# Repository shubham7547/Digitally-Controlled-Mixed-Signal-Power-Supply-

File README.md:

# Digitally Controlled Mixed-Signal Power Supply

[-orange.svg)]()

A high-performance, digitally controlled benchtop power supply that bridges digital precision with an ultra-fast analog regulation loop. The system delivers an adjustable **0 to 30.0 V** output at up to **1.0 A**, featuring dual rotary quadrature encoders with digit-level selection, high-resolution readbacks on a 2.8" color TFT display, and a non-blocking embedded firmware architecture.

Developed at the **Centre for Electronic Design and Technology (CEDT)**, **Netaji Subhas University of Technology (NSUT), New Delhi**.

---

## Table of Contents

- [Architectural Philosophy](#architectural-philosophy)
- [System Architecture](#system-architecture)
- [Key Specifications](#key-specifications)
- [Hardware & Circuit Design](#hardware--circuit-design)
  - [1. AC Input & Bulk Rectification](#1-ac-input--bulk-rectification)
  - [2. Dual Auxiliary Buck Regulators](#2-dual-auxiliary-buck-regulators)
  - [3. Digital Setpoint Generation](#3-digital-setpoint-generation)
  - [4. Analog Voltage Regulation Loop](#4-analog-voltage-regulation-loop)
  - [5. Current Sensing & Differential Amplification](#5-current-sensing--differential-amplification)
- [Pin Assignment Table](#pin-assignment-table)
- [Firmware Architecture](#firmware-architecture)
  - [Interrupt-Driven Quadrature Decoding](#interrupt-driven-quadrature-decoding)
  - [Non-Blocking Scheduling](#non-blocking-scheduling)
  - [Software Current Limit Foldback](#software-current-limit-foldback)
- [Repository Structure](#repository-structure)
- [Getting Started](#getting-started)
  - [Required Libraries](#required-libraries)
  - [Hardware Setup & Flashing](#hardware-setup--flashing)
- [Author & Affiliation](#author--affiliation)
- [License](#license)

---

## Architectural Philosophy

Simpler DIY microcontroller-based power supplies often place the digital microcontroller inside the primary feedback loop or use PWM/software loops to regulate output voltage, leading to slow transient response, ADC latency, and stability issues.

This design enforces a strict separation of concerns:
1. **Digital Setpoint Domain:** The **Arduino Nano** and **TLC5618A 12-bit DAC** determine what target voltage/current limit is desired. They never carry load current and never sit directly inside the fast closed loop.
2. **Analog Control Domain:** An **LM358 op-amp error amplifier** continuously compares the scaled output feedback against the DAC setpoint in real time, driving high-power series-pass transistors (**MJE2955T PNP**) instantaneously without digital latency.

---

## System Architecture

```mermaid
flowchart TD
    Mains["Mains 230V AC"] --> T1["Step-Down Transformer\n(Off-Board)"]
    T1 --> Bridge["Bridge Rectifier (1N4007)\n+ 2x 4700µF Series Caps (50V eff.)"]
    Bridge --> RawDC["Raw DC Bus (~36V Peak)"]

    RawDC --> VR6["LM2575 Buck 1\nStep-down to 5.29V"]
    VR6 --> MCU["Arduino Nano\n(5V Digital Rail)"]

    RawDC --> VR5["LM2575 Buck 2\nStep-down to 30.0V Rail"]
    VR5 --> OpAmp["LM358 Error Amplifier\n(Analog Rail)"]

    MCU -->|Hardware SPI| DAC["TLC5618A 12-Bit DAC\n(Vref Generation)"]
    DAC -->|Vref Setpoint| OpAmp

    RawDC --> PassTrans["MJE2955T Power Transistor\nSeries-Pass Output Stage"]
    OpAmp -->|Drive Base| PassTrans

    PassTrans --> Load["Output Terminal (0–30V, 0–1A)"]
    Load --> Shunt["Low-Side Current Shunt (0.3 Ω)"]

    Load -->|Voltage Divider (R4/R5)| MCU_ADC_V["ADC Pin A1 (V_sense)"]
    Load -->|Voltage Divider| OpAmp
    Shunt -->|Diff-Amp (LM358)| MCU_ADC_I["ADC Pin A0 (I_sense)"]

    MCU -->|Hardware SPI| TFT["ILI9341 320x240 Color TFT\nSet V/I, Out V/I, CV/CC"]
    Encoders["Dual Rotary Encoders\n+ Push Switches"] -->|Interrupts D2, D6| MCU
```

---

## Key Specifications

| Parameter | Specification | Notes |
| :--- | :--- | :--- |
| **Output Voltage Range** | $0.000\text{ V}$ to $30.000\text{ V}$ | Continuously adjustable |
| **Output Current Range** | $0.000\text{ A}$ to $1.000\text{ A}$ | Software-limited foldback |
| **Microcontroller** | Arduino Nano | ATmega328P @ 16 MHz |
| **DAC Resolution** | 12-bit ($4096\text{ steps}$) | TLC5618A Dual SPI DAC |
| **DAC Reference Voltage** | $1.090\text{ V}$ | Shared with internal ADC reference |
| **Voltage Control Gain** | $22.886\text{ V/V}$ | $V_{\text{out}} / V_{\text{dac}}$ |
| **Raw DC Bus Voltage** | $\approx 36\text{ V peak}$ | Rectified AC secondary |
| **Digital Auxiliary Rail** | $5.29\text{ V}$ | Regulated via LM2575-ADJ (VR6) |
| **Analog Auxiliary Rail** | $30.02\text{ V}$ | Regulated via LM2575-ADJ (VR5) |
| **Current Sense Shunt** | $0.3\ \Omega$ | Low-side shunt resistor |
| **Current Sense Gain** | $0.7398\text{ V/A}$ | $0.216 \times 3.425$ diff-amp gain |
| **Display** | 2.8" ILI9341 Color TFT | $320 \times 240$ resolution via SPI |
| **Voltage Digit Steps** | $1\text{ mV},\ 10\text{ mV},\ 100\text{ mV},\ 1\text{ V},\ 10\text{ V}$ | 5 selectable cursor positions |
| **Current Digit Steps** | $1\text{ mA},\ 10\text{ mA},\ 100\text{ mA},\ 1\text{ A}$ | 4 selectable cursor positions |

---

## Hardware & Circuit Design

### 1. AC Input & Bulk Rectification
* Off-board mains transformer secondary connects via a 2-pin heavy-duty terminal block.
* Rectification via a full-wave 1N4007 diode bridge produces a $\approx 36\text{ V}$ peak raw DC bus.
* Bulk filtering uses **two $4700\ \mu\text{F},\ 25\text{ V}$ electrolytic capacitors in series** ($C_2, C_4$) to double the effective breakdown voltage rating to $50\text{ V}$, well above the $36\text{ V}$ peak headroom.

### 2. Dual Auxiliary Buck Regulators
To supply both digital control logic and high-voltage analog regulation without wasting excessive power through linear dropouts, two independent LM2575 switching buck converters are employed:
* **VR6 (Digital 5.29V Rail):** $R_2 = 3.3\text{ k}\Omega,\ R_1 = 1\text{ k}\Omega \implies V_{\text{out}} = 1.23 \times (1 + 3300/1000) = 5.29\text{ V}$. Powers the Arduino 5V net and logic.
* **VR5 (Analog 30.0V Rail):** $R_2 = 110\text{ k}\Omega,\ R_1 = 4.7\text{ k}\Omega \implies V_{\text{out}} = 1.23 \times (1 + 110000/4700) = 30.02\text{ V}$. Powers the LM358 op-amp error amplifier stage.

### 3. Digital Setpoint Generation
* Uses a **TLC5618A** 12-bit dual-channel DAC over hardware SPI.
* Output Channel A generates the analog reference voltage $V_{\text{ref}}$, filtered by capacitor $C_1$.
* Calculated DAC code:
  $$\text{Code} = \left(\frac{V_{\text{target}} / 22.886}{2 \times 1.090}\right) \times 4096$$

### 4. Analog Voltage Regulation Loop
* Implemented with an **LM358** operational amplifier configured as a fast error amplifier:
  - Non-inverting input ($+$): $V_{\text{ref}}$ from the TLC5618A DAC.
  - Inverting input ($-$): $V_{\text{sense}}$ from the output voltage divider.
* Op-amp output directly drives the base of the series-pass power transistor (**MJE2955T PNP**). Any instantaneous load variation is corrected within microseconds by the analog loop without waiting for microcontroller polling.

### 5. Current Sensing & Differential Amplification
* Output current flows through a precision $0.3\ \Omega$ low-side shunt ($R_3$).
* The differential voltage is amplified by the second half of the LM358 package ($0.7398\text{ V/A}$) and routed directly to ADC channel `A0` for continuous readback and software foldback protection.

---

## Pin Assignment Table

| Arduino Nano Pin | Signal Name | Connected To | Function / Description |
| :--- | :--- | :--- | :--- |
| **D2** | `ENC_V_A` | Voltage Encoder Phase A | Hardware interrupt, quadrature phase A |
| **D3** | `ENC_V_B` | Voltage Encoder Phase B | Quadrature phase B input |
| **D4** | `ENC_V_SW` | Voltage Encoder Push Switch | Switch to cycle active voltage edit digit |
| **D5** | `ENC_I_SW` | Current Encoder Push Switch | Switch to cycle active current limit digit |
| **D6** | `ENC_I_A` | Current Encoder Phase A | Hardware interrupt, quadrature phase A |
| **D7** | `ENC_I_B` | Current Encoder Phase B | Quadrature phase B input |
| **D8** | `TFT_CD` | ILI9341 D/C Pin | Display Data / Command selection |
| **D9** | `TFT_CS` | ILI9341 CS Pin | Display Chip Select |
| **D10** | `DAC_CS` | TLC5618A ~CS Pin | DAC Chip Select |
| **D11** | `MOSI` | Shared SPI Bus | Hardware SPI Data Out (TFT + DAC) |
| **D12** | `MISO` | Shared SPI Bus | Hardware SPI Data In (unused) |
| **D13** | `SCK` | Shared SPI Bus | Hardware SPI Clock (TFT + DAC) |
| **A0** | `ADC_ISENSE` | Current-Sense Diff-Amp Out | Analog input, output current readback |
| **A1** | `ADC_VSENSE` | Output Voltage Divider Out | Analog input, output voltage readback |
| **AREF** | `Vref` | Shared Reference Net | Common 1.090V DAC reference / ADC ref |

---

## Firmware Architecture

The firmware (`adj_power_combined.ino`) implements a fully non-blocking architecture without any `delay()` calls:

### Interrupt-Driven Quadrature Decoding
* Both rotary encoders trigger pin-change interrupts on their Phase A signals (`D2` and `D6`).
* A 2-bit quadrature Gray-code state machine evaluates transition validity to reject switch bounce and deliver crisp rotation response.

### Non-Blocking Scheduling
* **Encoder & DAC update:** Handled immediately on knob turn or switch press ($200\text{ ms}$ debounce).
* **Sensor Acquisition Loop:** Runs on a dedicated $100\text{ ms}$ periodic cadence (`SENSE_INTERVAL_MS`).
* **TFT Refresh Loop:** Runs on a distinct $150\text{ ms}$ cadence (`DISPLAY_INTERVAL_MS`), rewriting only modified text fields to prevent screen flicker and bus contention.

### Software Current Limit Foldback
If the measured load current exceeds the user-configured current limit ($I_{\text{out}} > I_{\text{limit}}$):
1. The firmware flags `ccActive = true` and updates the UI status badge from **CV** (Green) to **CC** (Yellow).
2. The firmware automatically walks the DAC voltage setpoint downward in small incremental steps until load current falls back within bounds.
3. Once the overload is removed, the original voltage setpoint is automatically restored.

---

## Repository Structure

```
Benchtop-Power-Supply/
├── README.md                                    # Comprehensive project documentation
├── .gitignore                                   # KiCad temporary & backup ignore rules
├── Block Diagram/
│   └── block_diagram.png                        # High-level system architecture block diagram
├── Code Files/
│   └── adj_power_combined/
│       └── adj_power_combined.ino               # Non-blocking firmware for Arduino Nano
├── Datasheet/
│   ├── LM2575.PDF                               # Step-down switching regulator datasheet
│   ├── lm358.pdf                                # Dual operational amplifier datasheet
│   ├── MJE2955T.PDF                             # PNP silicon power transistor datasheet
│   └── TLC5618.PDF                              # Dual 12-bit digital-to-analog converter datasheet
├── Kicad Files/
│   └── Adj_power/
│       ├── Adj_power.kicad_sch                  # KiCad schematic design
│       ├── Adj_power.kicad_pcb                  # KiCad printed circuit board layout
│       ├── Adj_power.kicad_pro                  # KiCad project file
│       ├── Adj_power.pdf                        # Printable schematic diagram PDF
│       └── bom/
│           └── ibom.html                        # Interactive HTML Bill of Materials
├── Report/
│   └── pwr_supply.pdf                           # Full technical engineering report document
└── Report Source File/
    └── pwr_supply/
        ├── adj_power_combined.ino               # Firmware source copy
        ├── block_diagram.png                    # Block diagram graphic
        ├── cedtnew.png                          # Institutional logo
        └── schematic.jpg                        # Circuit schematic render
```

---

## Getting Started

### Required Libraries
Install the following libraries via the Arduino Library Manager or place them in your `libraries/` directory:
- **SPI** (Standard Arduino SPI library)
- **LCDWIKI_GUI** (Graphical primitives)
- **LCDWIKI_SPI** (Hardware SPI driver for ILI9341)

### Hardware Setup & Flashing
1. Connect your **Arduino Nano** to your PC via USB.
2. Open `Code Files/adj_power_combined/adj_power_combined.ino` in Arduino IDE.
3. Configure your IDE settings under **Tools**:
   - **Board:** Arduino Nano
   - **Processor:** ATmega328P (or *ATmega328P (Old Bootloader)*)
   - **Port:** Select the corresponding COM port.
4. Verify and **Upload** the firmware sketch.
5. The ILI9341 display will illuminate and render the default UI with $0.000\text{ V}$ setpoint and $1.000\text{ A}$ current limit in **CV** mode.

---

## Author & Affiliation

* **Shubham Kumar**

**Centre for Electronic Design and Technology (CEDT)**  
**Netaji Subhas University of Technology (NSUT), New Delhi**  
*Project Date: March 2026*

---

## License

This project is open-source hardware and software available under the [MIT License](LICENSE).

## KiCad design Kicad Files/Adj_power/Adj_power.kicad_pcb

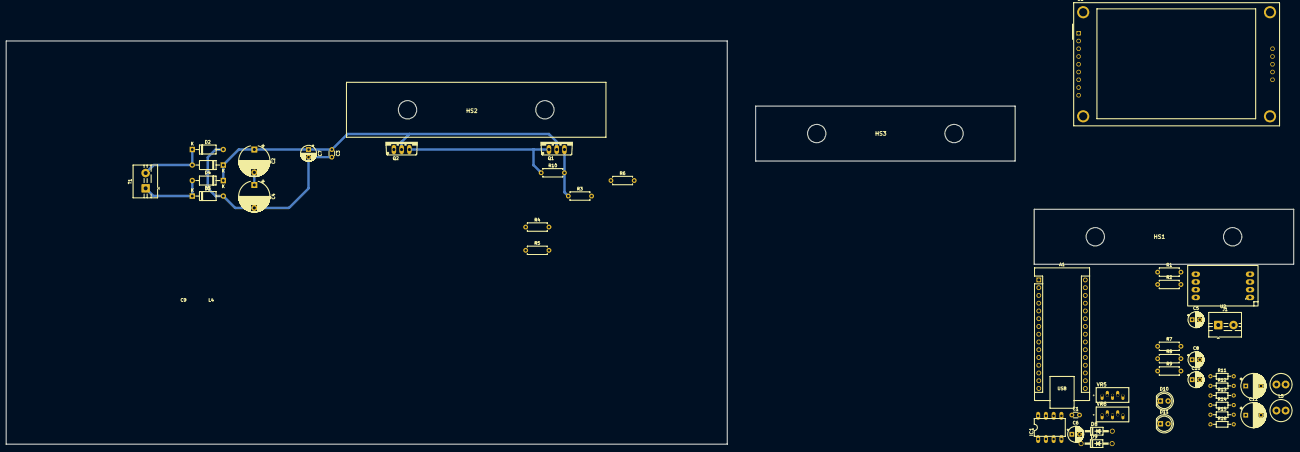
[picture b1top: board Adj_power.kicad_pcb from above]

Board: 2 copper layers, 421.8 x 132.1 mm, 50 parts (0 on the bottom side), 32 nets.

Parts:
A1: Arduino_Nano_Every; Arduino_Nano
C1: C; C_Disc_D3.0mm_W1.6mm_P2.50mm
C2, C4: 4700uF; CP_Radial_D10.0mm_P7.50mm
C3: 0.1u; C_Disc_D3.0mm_W1.6mm_P2.50mm
C5: 470uF; CP_Radial_D5.0mm_P2.50mm
C6: 100nF; CP_Radial_D5.0mm_P2.50mm
C7: 10uF; CP_Radial_D5.0mm_P2.50mm
C8, C10: 100uF; CP_Radial_D5.0mm_P2.50mm
C9, C11: 1000uF; CP_Radial_D8.0mm_P5.00mm
D1, D2, D3, D4: D_45deg_Filled; D_A-405_P10.16mm_Horizontal
D8, D9: DO41-10
D10, D11: LED; LED_D5.0mm
HS1, HS2, HS3: Heatsink; HEATSINK
IC1: DIL08
J1: Screw_Terminal_01x02; TerminalBlock_MaiXu_MX126-5.0-02P_1x02_P5.00mm
L4: 470uH; L_Radial_D7.0mm_P3.00mm
L5: 100uH; L_Radial_D7.0mm_P3.00mm
Q1, Q2: MJE3055; TO220AV
R1: 4.7K; R_Axial_DIN0207_L6.3mm_D2.5mm_P7.62mm_Horizontal
R2: 220; R_Axial_DIN0207_L6.3mm_D2.5mm_P7.62mm_Horizontal
R3: 0.3; R_Axial_DIN0207_L6.3mm_D2.5mm_P7.62mm_Horizontal
R4: 46k; R_Axial_DIN0207_L6.3mm_D2.5mm_P7.62mm_Horizontal
R5, R8, R9: 2.2K; R_Axial_DIN0207_L6.3mm_D2.5mm_P7.62mm_Horizontal
R6, R7: 1K; R_Axial_DIN0207_L6.3mm_D2.5mm_P7.62mm_Horizontal
R10: 470; R_Axial_DIN0207_L6.3mm_D2.5mm_P7.62mm_Horizontal
R11: 47k; R_Axial_DIN0204_L3.6mm_D1.6mm_P7.62mm_Horizontal
R12: 1.5k; R_Axial_DIN0204_L3.6mm_D1.6mm_P7.62mm_Horizontal
R13: 3.3K; R_Axial_DIN0204_L3.6mm_D1.6mm_P7.62mm_Horizontal
R14, R16: 330; R_Axial_DIN0204_L3.6mm_D1.6mm_P7.62mm_Horizontal
R15: 1K; R_Axial_DIN0204_L3.6mm_D1.6mm_P7.62mm_Horizontal
T1: Transformer_1P_1S; TerminalBlock_MaiXu_MX126-5.0-02P_1x02_P5.00mm
U1: CR2013-MI2120
U2: TLC5618AQD; BOB
VR5, VR6: TO170P1067X483X1651-5

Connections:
+5V: C1.1, U2.8 (VDD)
D/C: A1.11 (D8), U1.5 (D/~C)
GND: A1.4 (GND), A1.29 (GND), C1.2, C3.2, C4.2, C5.2, C7.2, C8.1, C9.2, C10.1, C11.2, D1.2 (A), D2.2 (A), D8.A, D9.A, D10.1 (K), D11.1 (K), IC1.4 (V-), J1.2, R5.2, R8.1, R12.2, R15.2, T1.2 (AB), U1.2 (GND), U2.5 (AGND), VR5.3 (GROUND), VR5.5 (~ON/OFF), VR6.3 (GROUND), VR6.5 (~ON/OFF)
I_sense: A1.19 (A0), IC1.7 (OUT), R9.1
LED: A1.17 (3V3), U1.8 (LED)
MOSI: A1.14 (MOSI), U1.6 (MOSI), U2.1 (DIN)
unnamed: A1.13 (D10), U2.3 (~CS)
unnamed: C2.2, C4.1
unnamed: C6.2, R1.2
unnamed: D1.1 (K), D3.2 (A)
unnamed: D2.1 (K), D4.2 (A)
unnamed: D10.2 (A), R14.2
unnamed: D11.2 (A), R16.2
unnamed: IC1.3 (+IN), U2.4 (OUT_A)
unnamed: C6.1, IC1.1 (OUT), R2.1
unnamed: IC1.5 (+IN), R6.2, R8.2
unnamed: IC1.6 (-IN), R7.2, R9.2
unnamed: C5.1, J1.1, R3.2, R4.1, R7.1
unnamed: Q1.B, Q2.E, R10.1
unnamed: Q1.E, R3.1, R6.1, R10.2
unnamed: Q2.B, R2.2
unnamed: R11.2, R12.1, VR5.4 (FEEDBACK)
unnamed: D8.C, L4.1, VR5.2 (OUTPUT)
unnamed: R13.2, R15.1, VR6.4 (FEEDBACK)
unnamed: D9.C, L5.1, VR6.2 (OUTPUT)
PWR_ard: A1.27 (+5V), C11.1, L5.2, R13.1, R16.1, U1.1 (VCC)
PWR_op-amp: C9.1, IC1.8 (V+), L4.2, R11.1, R14.1
Raw_DC: C2.1, C3.1, C7.1, C8.2, C10.2, D3.1 (K), D4.1 (K), Q1.C, Q2.C, VR5.1 (VIN), VR6.1 (VIN)
SCK: A1.16 (SCK), U1.7 (SCK), U2.2 (SCLK)
TFT_CS: A1.12 (D9), U1.3 (~CS)
V_sense: A1.20 (A1), IC1.2 (-IN), R1.1, R4.2, R5.1
Vref: A1.18 (AREF), U2.6 (REFIN)

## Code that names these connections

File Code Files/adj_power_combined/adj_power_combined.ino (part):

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// ---------------------------------------------------------------------------
#define MODEL     ILI9341

#define TFT_CS     9
#define TFT_CD     8            // D/C
#define TFT_MISO  12            // hw SPI, unused by TFT but constructor wants it
#define TFT_MOSI  11            // hw SPI
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#define ENC_I_B    7            // RE_4
#define ENC_I_SW   5            // SW_2

#define ADC_ISENSE A0           // I_sense
#define ADC_VSENSE A1           // V_sense

// ---------------------------------------------------------------------------
// CALIBRATION CONSTANTS
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
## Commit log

2026-03-15 Initial commit: Digitally Controlled Mixed-Signal Power Supply
2026-03-15 Update output current specification to 1.0 A
2026-03-15 Update microcontroller reference to Arduino Nano (ATmega328P)
